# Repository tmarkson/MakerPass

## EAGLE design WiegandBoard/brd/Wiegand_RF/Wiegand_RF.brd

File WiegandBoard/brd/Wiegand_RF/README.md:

#MakerPass Wiegand Board ESP8266

###Tasks
See the schematic for pending task list

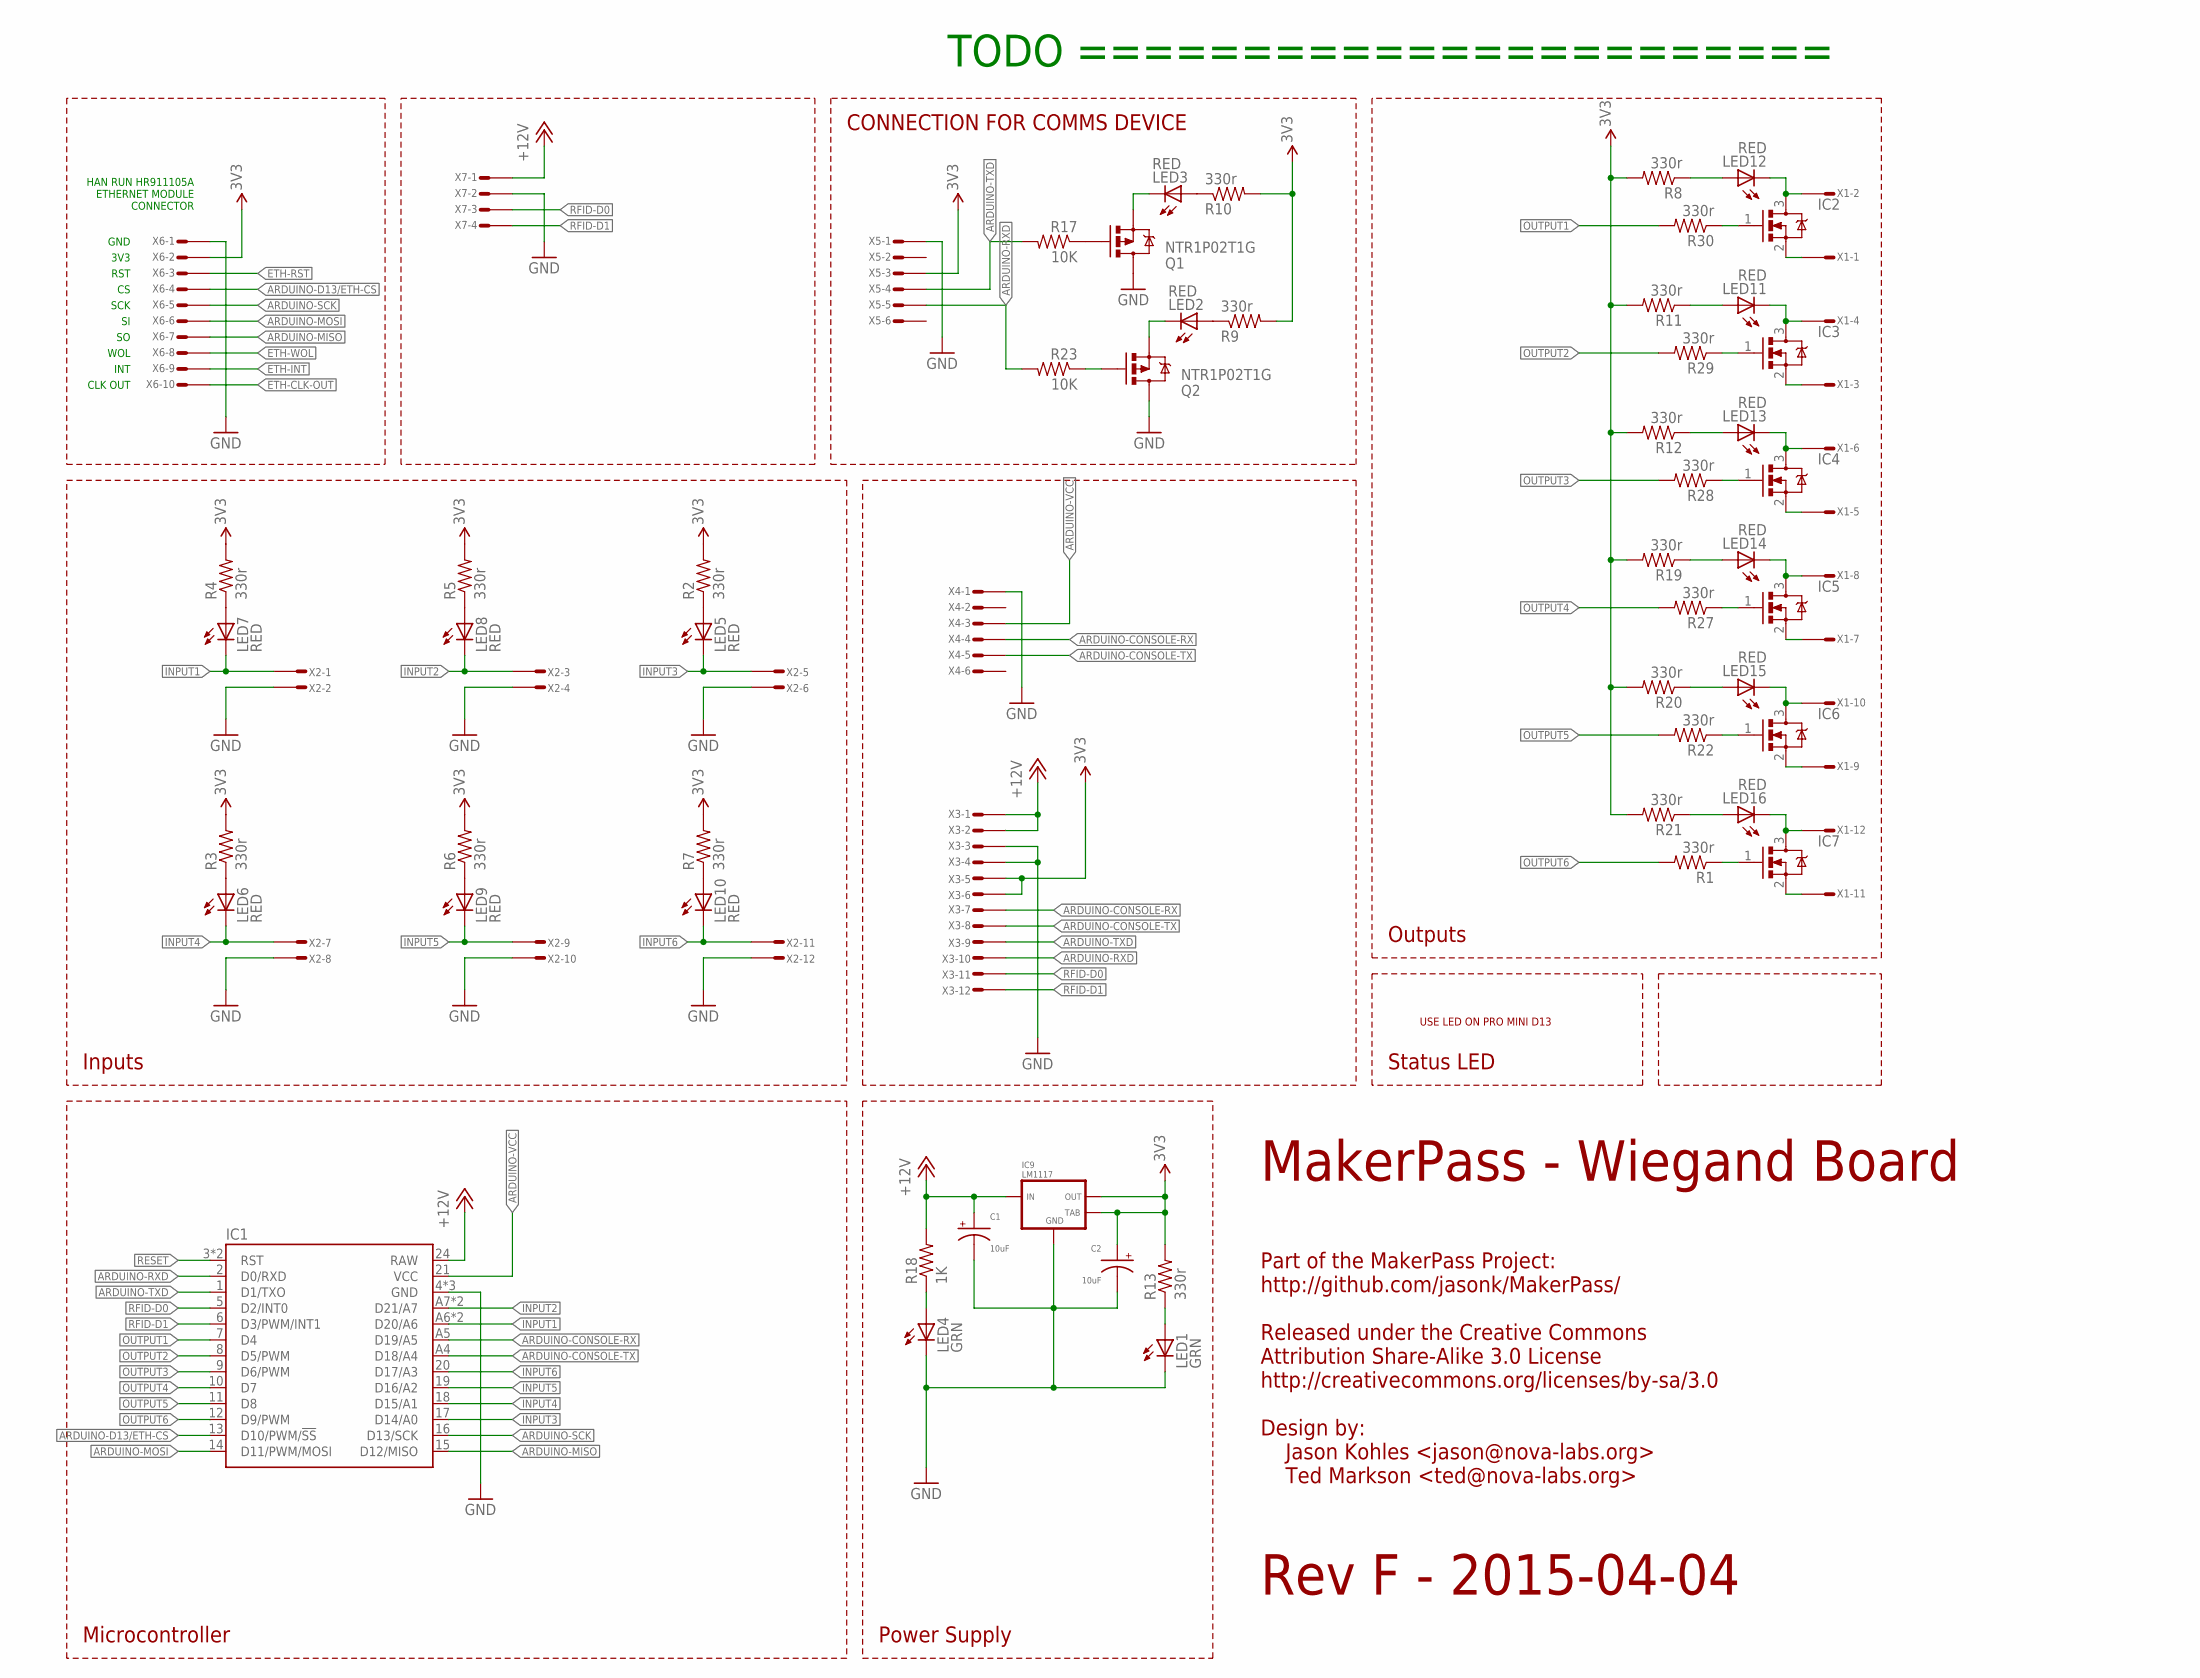
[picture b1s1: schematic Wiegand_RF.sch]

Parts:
C1, C2: 10uF; C-CAN-4.3; MFG_PN EMVA250ADA100MD55G
IC1: ARDUINO-PRO-MINI-ALIEXPRESS
IC2, IC3, IC4, IC5, IC6, IC7: MOSFET-NCHANNEL-SOT23; SOT23
IC9: LM1117; SOT223; MFG_PN LM1117MPX-3.3/NOPB
LED1, LED4: GRN; LED-805; MFG_PN LG R971-KN-1
LED2, LED3, LED5, LED6, LED7, LED8, LED9, LED10, LED11, LED12, LED13, LED14, LED15, LED16: RED; LED-805; MFG_PN LY R976-PS-36
Q1, Q2: NTR1P02T1G; SOT23-3; MFG_PN NTR1P02T1G
R1, R2, R3, R4, R5, R6, R7, R8, R9, R10, R11, R12, R13, R19, R20, R21, R22, R27, R28, R29, R30: 330r; 0603-RES; MFG_PN ERJ3EKF3300V
R17, R23: 10K; 0603-RES; MFG_PN ERJ3EKF1002V
R18: 1K; 0603-RES; MFG_PN ERJ3EKF1001V
X1, X2, X3: CON-1X12-TERMBLOCK-3.5MM; MFG_PN OSTTE120104
X4, X5: CON-1X6-FTDI-AVR
X6: CON-2X5
X7: CON-1X4

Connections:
3V3: C2.+, IC9.OUT, IC9.TAB, R2.2, R3.2, R4.2, R5.2, R6.2, R7.2, R8.2, R9.2, R10.2, R11.2, R12.2, R13.2, R19.2, R20.2, R21.2, X3.5, X3.6, X5.3, X6.2
+12V: C1.+, IC1.24 (RAW), IC9.IN, R18.2, X3.1, X3.2, X7.1
ARDUINO-CONSOLE-RX: IC1.A5 (D19/A5), X3.7, X4.4
ARDUINO-CONSOLE-TX: IC1.A4 (D18/A4), X3.8, X4.5
ARDUINO-D13/ETH-CS: IC1.13 (D10/PWM/!SS), X6.4
ARDUINO-MISO: IC1.15 (D12/MISO), X6.7
ARDUINO-MOSI: IC1.14 (D11/PWM/MOSI), X6.6
ARDUINO-RXD: IC1.2 (D0/RXD), R23.2, X3.10, X5.5
ARDUINO-SCK: IC1.16 (D13/SCK), X6.5
ARDUINO-TXD: IC1.1 (D1/TXO), R17.2, X3.9, X5.4
ARDUINO-VCC: IC1.21 (VCC), X4.3
ETH-CLK-OUT: X6.10
ETH-INT: X6.9
ETH-RST: X6.3
ETH-WOL: X6.8
GND: C1.-, C2.-, IC1.4 (GND), IC1.23 (GND), IC1.25 (GND), IC9.GND, LED1.C, LED4.C, Q1.3 (D), Q2.3 (D), X2.2, X2.4, X2.6, X2.8, X2.10, X2.12, X3.3, X3.4, X4.1, X5.1, X6.1, X7.2
INPUT1: IC1.A6 (D20/A6), IC1.A6@2 (D20/A6), LED7.C, X2.1
INPUT2: IC1.A7 (D21/A7), IC1.A7@2 (D21/A7), LED8.C, X2.3
INPUT3: IC1.17 (D14/A0), LED5.C, X2.5
INPUT4: IC1.18 (D15/A1), LED6.C, X2.7
INPUT5: IC1.19 (D16/A2), LED9.C, X2.9
INPUT6: IC1.20 (D17/A3), LED10.C, X2.11
unnamed: LED1.A, R13.1
unnamed: IC6.2 (S), X1.9
unnamed: IC6.3 (D), LED15.C, X1.10
unnamed: LED5.A, R2.1
unnamed: LED4.A, R18.1
unnamed: LED3.C, Q1.2 (S)
unnamed: LED6.A, R3.1
unnamed: LED7.A, R4.1
unnamed: LED8.A, R5.1
unnamed: LED9.A, R6.1
unnamed: LED10.A, R7.1
unnamed: LED12.A, R8.1
unnamed: IC2.2 (S), X1.1
unnamed: IC2.3 (D), LED12.C, X1.2
unnamed: IC3.2 (S), X1.3
unnamed: IC4.3 (D), LED13.C, X1.6
unnamed: LED11.A, R11.1
unnamed: IC4.2 (S), X1.5
unnamed: LED13.A, R12.1
unnamed: LED2.A, R9.1
unnamed: LED3.A, R10.1
unnamed: IC5.2 (S), X1.7
unnamed: IC5.3 (D), LED14.C, X1.8
unnamed: LED14.A, R19.1
unnamed: LED2.C, Q2.2 (S)
unnamed: Q1.1 (G), R17.1
unnamed: LED15.A, R20.1
unnamed: IC7.2 (S), X1.11
unnamed: IC7.3 (D), LED16.C, X1.12
unnamed: LED16.A, R21.1
unnamed: IC7.1 (G), R1.1
unnamed: Q2.1 (G), R23.1
unnamed: IC2.1 (G), R30.1
unnamed: IC3.1 (G), R29.1
unnamed: IC4.1 (G), R28.1
unnamed: IC5.1 (G), R27.1
unnamed: IC6.1 (G), R22.1
unnamed: IC3.3 (D), LED11.C, X1.4
OUTPUT1: IC1.7 (D4), R30.2
OUTPUT2: IC1.8 (D5/PWM), R29.2
OUTPUT3: IC1.9 (D6/PWM), R28.2
OUTPUT4: IC1.10 (D7), R27.2
OUTPUT5: IC1.11 (D8), R22.2
OUTPUT6: IC1.12 (D9/PWM), R1.2
RESET: IC1.3 (RST), IC1.22 (RST)
RFID-D0: IC1.5 (D2/INT0), X3.11, X7.3
RFID-D1: IC1.6 (D3/PWM/INT1), X3.12, X7.4

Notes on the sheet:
CONNECTION FOR COMMS DEVICE
Power Supply
Part of the MakerPass Project: http://github.com/jasonk/MakerPass/ Released under the Creative Commons Attribution Share-Alike 3.0 License http://creativecommons.org/licenses/by-sa/3.0 Design by: Jason Kohles <jason@nova-labs.org> Ted Markson <ted@nova-labs.org>
Status LED
Outputs
Inputs
Microcontroller
MakerPass - Wiegand Board
Rev F - 2015-04-04
TODO =======================
USE LED ON PRO MINI D13
HAN RUN HR911105A ETHERNET MODULE CONNECTOR
GND
3V3
RST
SCK
WOL
INT
CLK OUT

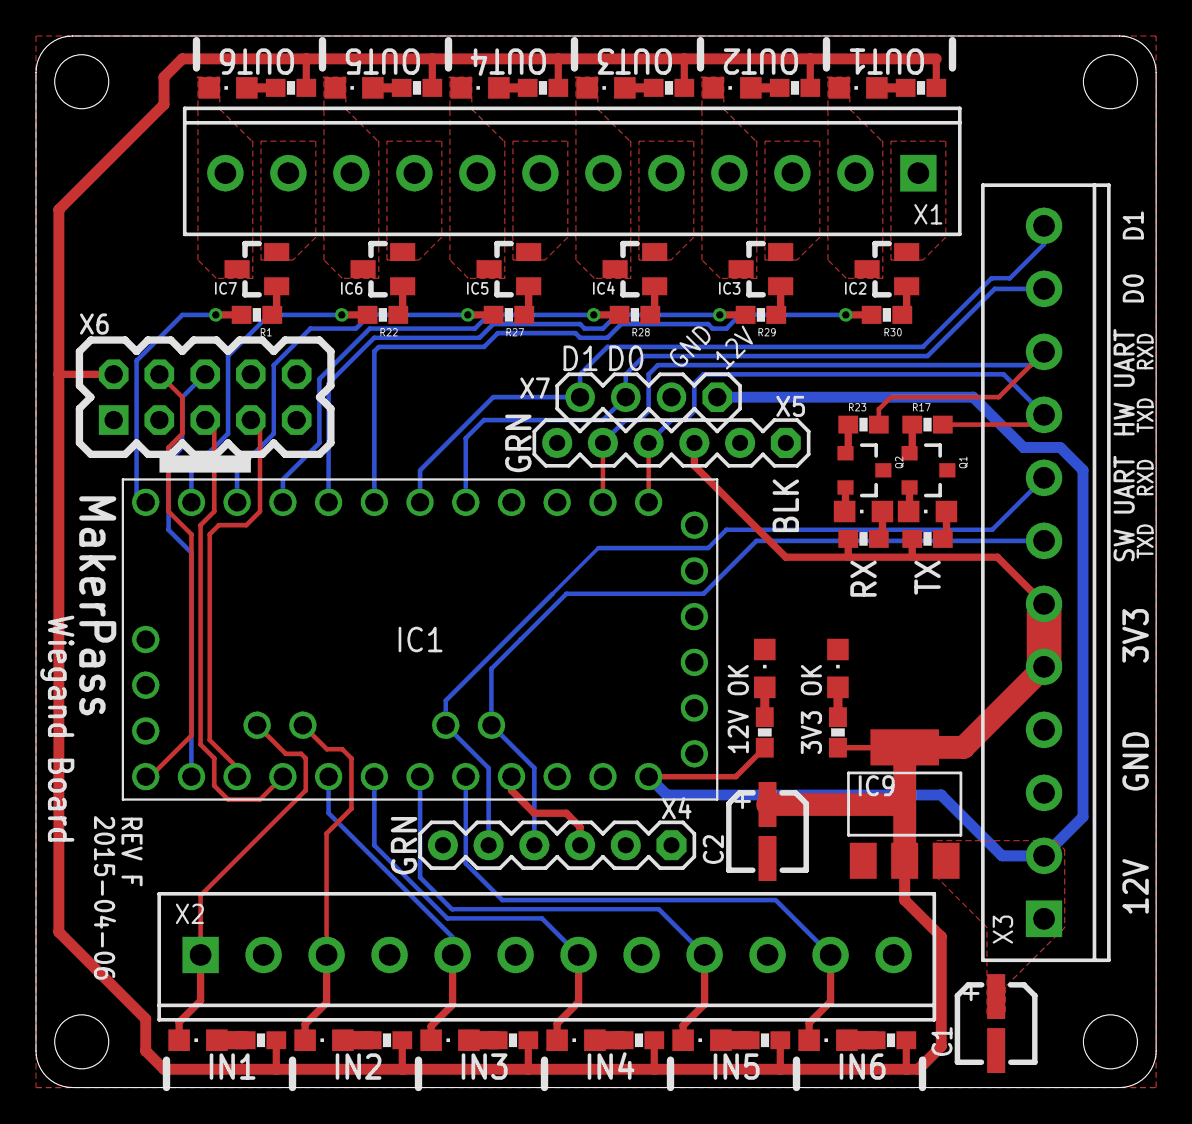
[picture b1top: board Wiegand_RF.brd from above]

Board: 2 copper layers, 62.2 x 58.4 mm, 60 parts (1 on the bottom side), 65 nets.

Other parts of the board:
U$1: NOVA-LABS-LOGO-FULL-SMALL

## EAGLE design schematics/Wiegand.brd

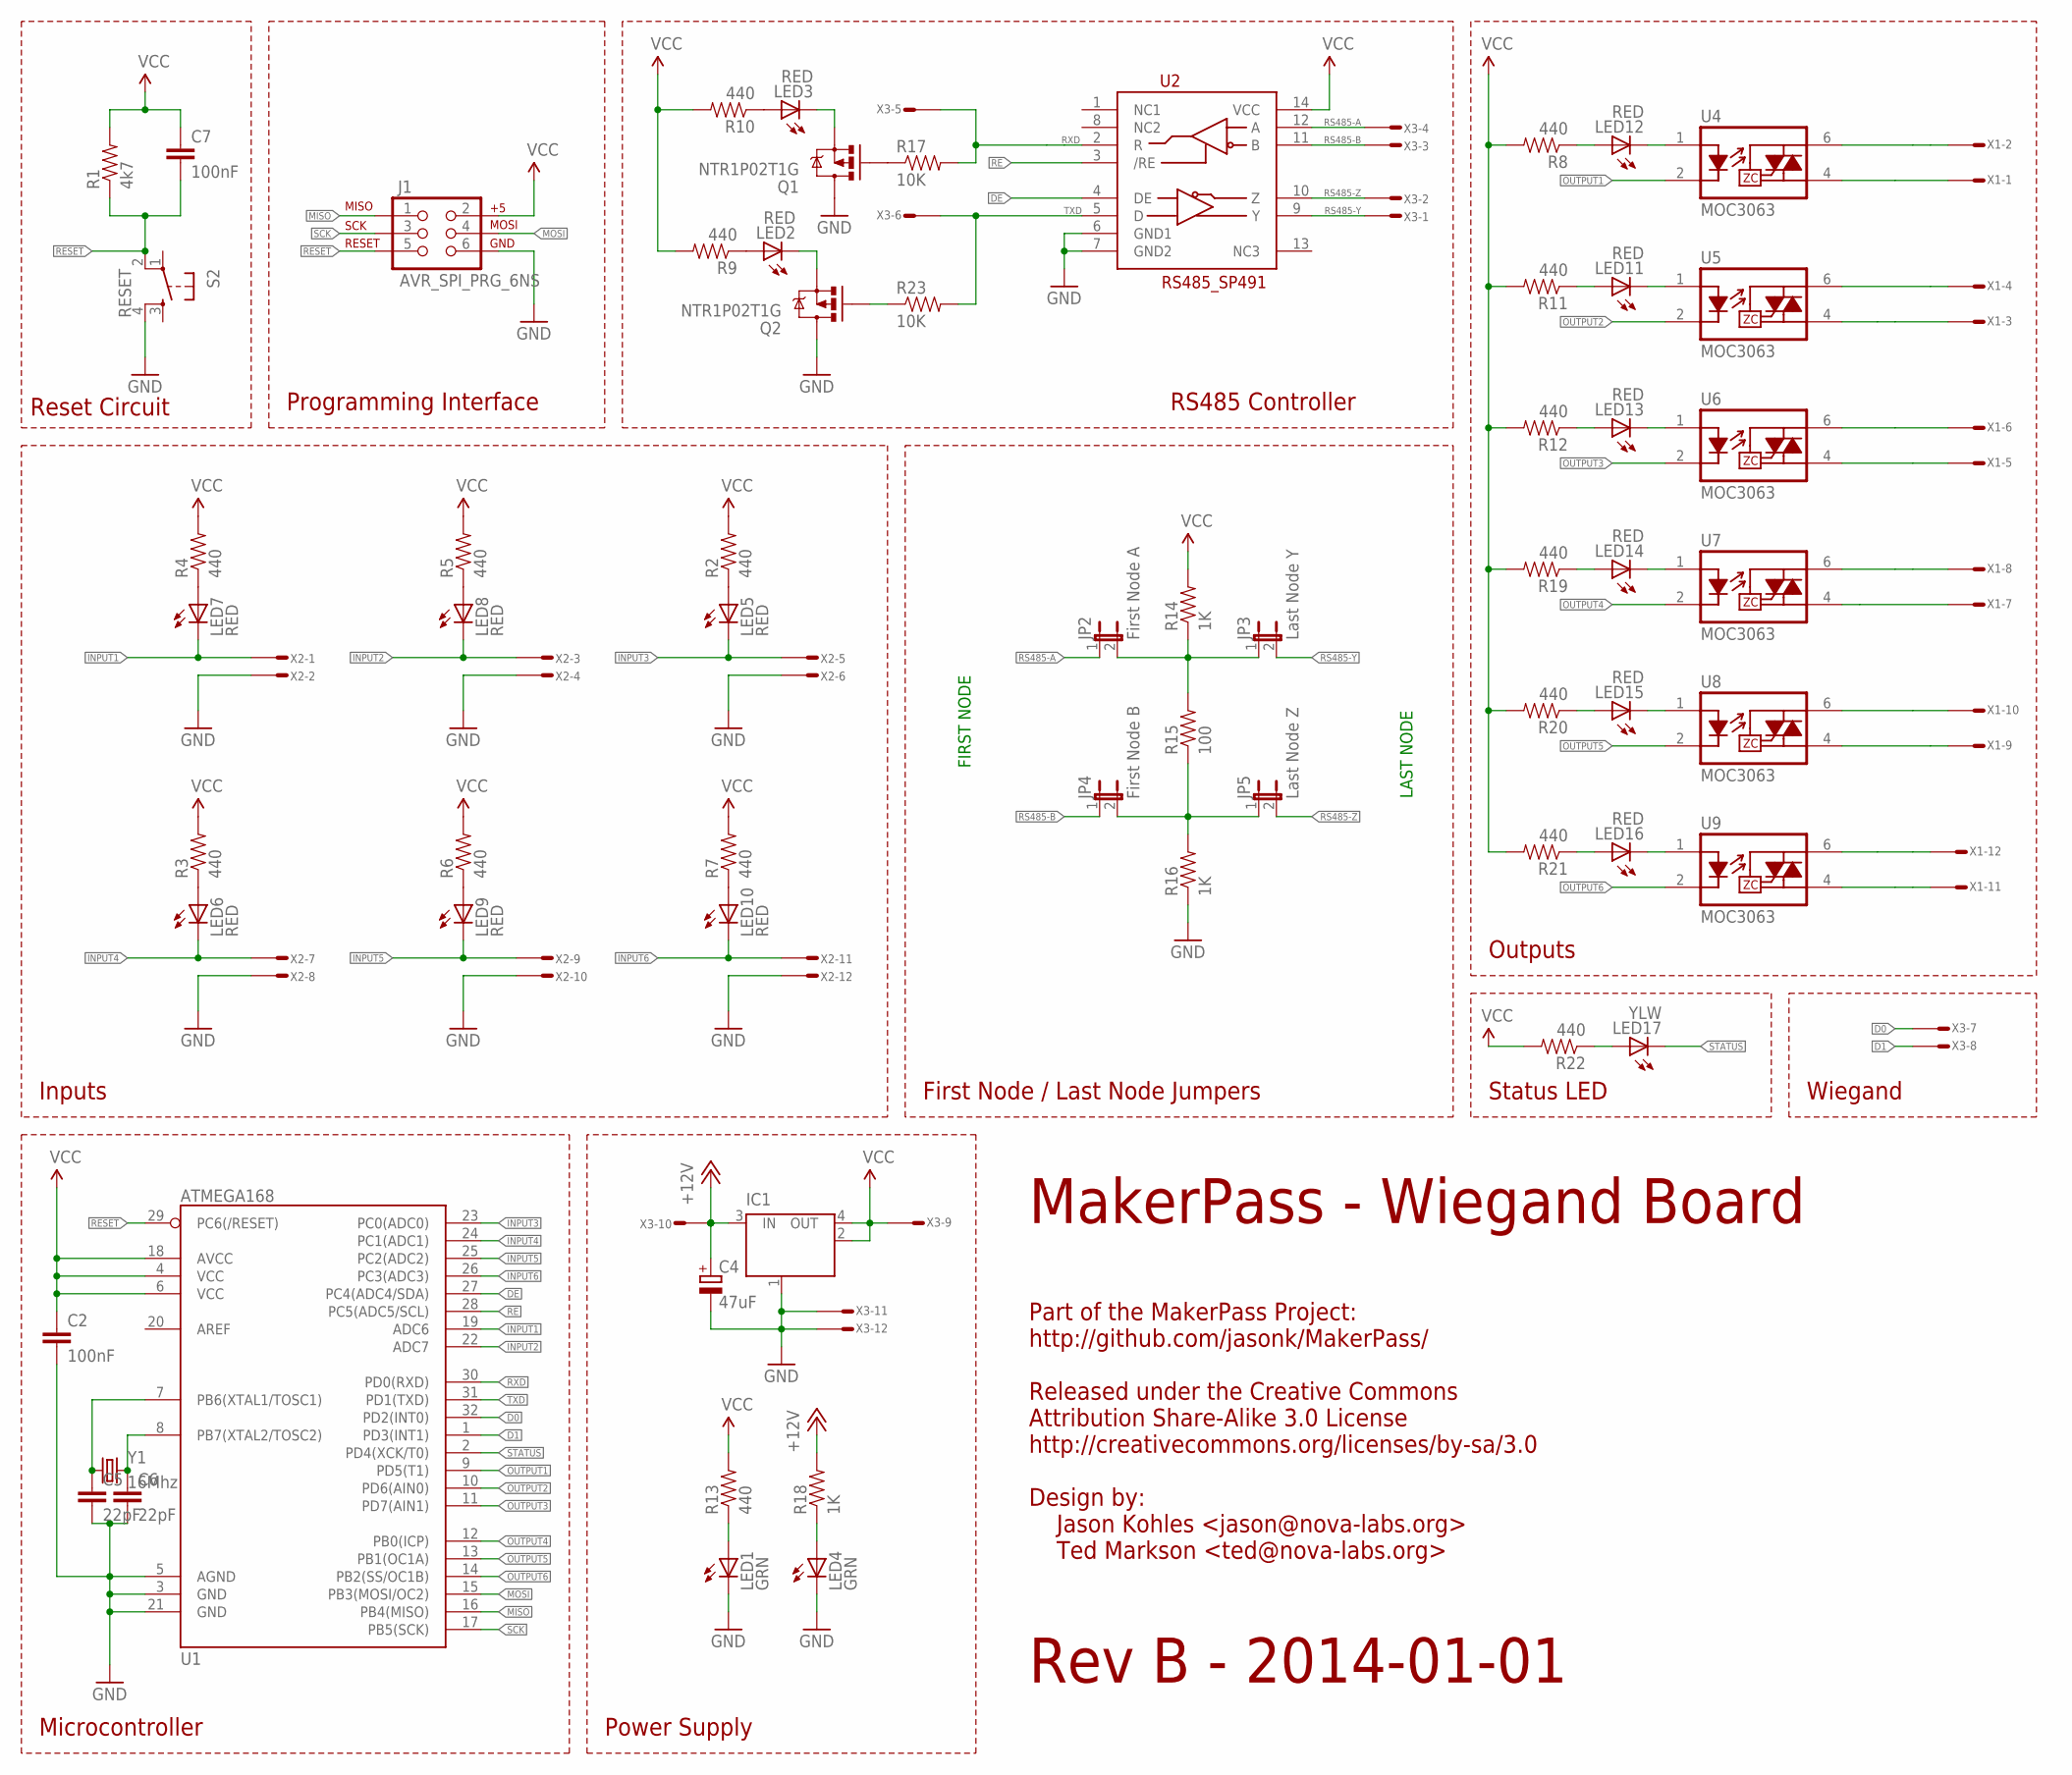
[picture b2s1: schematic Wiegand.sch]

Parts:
C2, C7: 100nF; 0603-CAP; MFG_PN 0603YC104KAT2A
C4: 47uF; PANASONIC_D; MFG_PN EMVA250ADA470MF55G
C5, C6: 22pF; 0603-CAP; MFG_PN 06035A220JAT2A
IC1: MC33269ST-3.3T3; SOT223; MFG_PN NCP1117ST50T3G
J1: AVR_SPI_PRG_6NS; 2X3-NS
JP2: First Node A; 1X02; MFG_PN 1x2 pin header
JP3: Last Node Y; 1X02; MFG_PN 1x2 pin header
JP4: First Node B; 1X02; MFG_PN 1x2 pin header
JP5: Last Node Z; 1X02; MFG_PN 1x2 pin header
LED1, LED4: GRN; LED-805; MFG_PN LG R971-KN-1
LED2, LED3, LED5, LED6, LED7, LED8, LED9, LED10, LED11, LED12, LED13, LED14, LED15, LED16: RED; LED-805; MFG_PN LY R976-PS-36
LED17: YLW; LED-805; MFG_PN LY R976-PS-36
Q1, Q2: NTR1P02T1G; SOT23-3; MFG_PN NTR1P02T1G
R1: 4k7; 0603-RES; MFG_PN ERJ-3GEYJ472V
R2, R3, R4, R5, R6, R7, R8, R9, R10, R11, R12, R13, R19, R20, R21, R22: 440; 0603-RES; MFG_PN ERJ3EKF3300V
R14, R16, R18: 1K; 0603-RES; MFG_PN ERJ-3EKF1001V
R15: 100; 0603-RES; MFG_PN ERJ-3EKF1001V
R17, R23: 10K; 0603-RES; MFG_PN ERJ3EKF3300V
S2: RESET; TACTILE_SWITCH_SMD; MFG_PN PTS525SM10SMTRLFS
U1: ATMEGA168; TQFP32-08; MFG_PN ATMEGA168-20AU
U2: RS485_SP491; SOIC-14; MFG_PN SP491EEN-L
U4, U5, U6, U7, U8, U9: MOC3063; DIP8SMD; MFG_PN MOC3063M
X1, X2, X3: CON-1X12-TERMBLOCK-3.5MM; MFG_PN OSTTE120104
Y1: 16Mhz; HC49UP; MFG_PN FOXSDLF/160-20

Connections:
+12V: C4.+, IC1.3 (IN), R18.2, X3.10
D0: U1.32 (PD2(INT0)), X3.7
D1: U1.1 (PD3(INT1)), X3.8
DE: U1.27 (PC4(ADC4/SDA)), U2.4 (DE)
GND: C2.2, C4.-, C5.2, C6.2, IC1.1 (GND/ADJ), J1.6, LED1.C, LED4.C, Q1.3 (D), Q2.3 (D), R16.1, S2.4, U1.3 (GND), U1.5 (AGND), U1.21 (GND), U2.6 (GND1), U2.7 (GND2), X2.2, X2.4, X2.6, X2.8, X2.10, X2.12, X3.11, X3.12
INPUT1: LED7.C, U1.19 (ADC6), X2.1
INPUT2: LED8.C, U1.22 (ADC7), X2.3
INPUT3: LED5.C, U1.23 (PC0(ADC0)), X2.5
INPUT4: LED6.C, U1.24 (PC1(ADC1)), X2.7
INPUT5: LED9.C, U1.25 (PC2(ADC2)), X2.9
INPUT6: LED10.C, U1.26 (PC3(ADC3)), X2.11
MISO: J1.1, U1.16 (PB4(MISO))
MOSI: J1.4, U1.15 (PB3(MOSI/OC2))
unnamed: LED1.A, R13.1
unnamed: U8.4 (T2), X1.9
unnamed: U8.6 (T1), X1.10
unnamed: LED5.A, R2.1
unnamed: JP4.2, JP5.1, R15.1, R16.2
unnamed: JP2.2, JP3.1, R14.1, R15.2
unnamed: LED4.A, R18.1
unnamed: LED3.C, Q1.2 (S)
unnamed: LED6.A, R3.1
unnamed: LED7.A, R4.1
unnamed: LED8.A, R5.1
unnamed: LED9.A, R6.1
unnamed: LED10.A, R7.1
unnamed: LED12.C, U4.1 (A)
unnamed: LED12.A, R8.1
unnamed: U4.4 (T2), X1.1
unnamed: U4.6 (T1), X1.2
unnamed: U5.4 (T2), X1.3
unnamed: U5.6 (T1), X1.4
unnamed: LED11.A, R11.1
unnamed: LED11.C, U5.1 (A)
unnamed: U6.4 (T2), X1.5
unnamed: U6.6 (T1), X1.6
unnamed: LED13.A, R12.1
unnamed: LED2.A, R9.1
unnamed: LED3.A, R10.1
unnamed: LED13.C, U6.1 (A)
unnamed: U7.4 (T2), X1.7
unnamed: U7.6 (T1), X1.8
unnamed: LED14.A, R19.1
unnamed: LED14.C, U7.1 (A)
unnamed: LED2.C, Q2.2 (S)
unnamed: Q1.1 (G), R17.1
unnamed: LED15.A, R20.1
unnamed: LED15.C, U8.1 (A)
unnamed: U9.4 (T2), X1.11
unnamed: U9.6 (T1), X1.12
unnamed: LED16.A, R21.1
unnamed: LED16.C, U9.1 (A)
unnamed: LED17.A, R22.1
unnamed: Q2.1 (G), R23.1
unnamed: C5.1, U1.7 (PB6(XTAL1/TOSC1)), Y1.1
unnamed: C6.1, U1.8 (PB7(XTAL2/TOSC2)), Y1.2
OUTPUT1: U1.9 (PD5(T1)), U4.2 (K)
OUTPUT2: U1.10 (PD6(AIN0)), U5.2 (K)
OUTPUT3: U1.11 (PD7(AIN1)), U6.2 (K)
OUTPUT4: U1.12 (PB0(ICP)), U7.2 (K)
OUTPUT5: U1.13 (PB1(OC1A)), U8.2 (K)
OUTPUT6: U1.14 (PB2(SS/OC1B)), U9.2 (K)
RE: U1.28 (PC5(ADC5/SCL)), U2.3 (/RE)
RESET: C7.2, J1.5, R1.1, S2.2, U1.29 (PC6(/RESET))
RS485-A: JP2.1, U2.12 (A), X3.4
RS485-B: JP4.1, U2.11 (B), X3.3
RS485-Y: JP3.2, U2.9 (Y), X3.1
RS485-Z: JP5.2, U2.10 (Z), X3.2
RXD: R17.2, U1.30 (PD0(RXD)), U2.2 (R), X3.5
SCK: J1.3, U1.17 (PB5(SCK))
STATUS: LED17.C, U1.2 (PD4(XCK/T0))
TXD: R23.2, U1.31 (PD1(TXD)), U2.5 (D), X3.6
VCC: C2.1, C7.1, IC1.2 (OUT), IC1.4 (OUT), J1.2, R1.2, R2.2, R3.2, R4.2, R5.2, R6.2, R7.2, R8.2, R9.2, R10.2, R11.2, R12.2, R13.2, R14.2, R19.2, R20.2, R21.2, R22.2, U1.4 (VCC), U1.6 (VCC), U1.18 (AVCC), U2.14 (VCC), X3.9

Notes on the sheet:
RS485 Controller
Programming Interface
Power Supply
Reset Circuit
Wiegand
Part of the MakerPass Project: http://github.com/jasonk/MakerPass/ Released under the Creative Commons Attribution Share-Alike 3.0 License http://creativecommons.org/licenses/by-sa/3.0 Design by: Jason Kohles <jason@nova-labs.org> Ted Markson <ted@nova-labs.org>
Status LED
First Node / Last Node Jumpers
Outputs
Inputs
Microcontroller
MakerPass - Wiegand Board
Rev B - 2014-01-01
FIRST NODE
LAST NODE

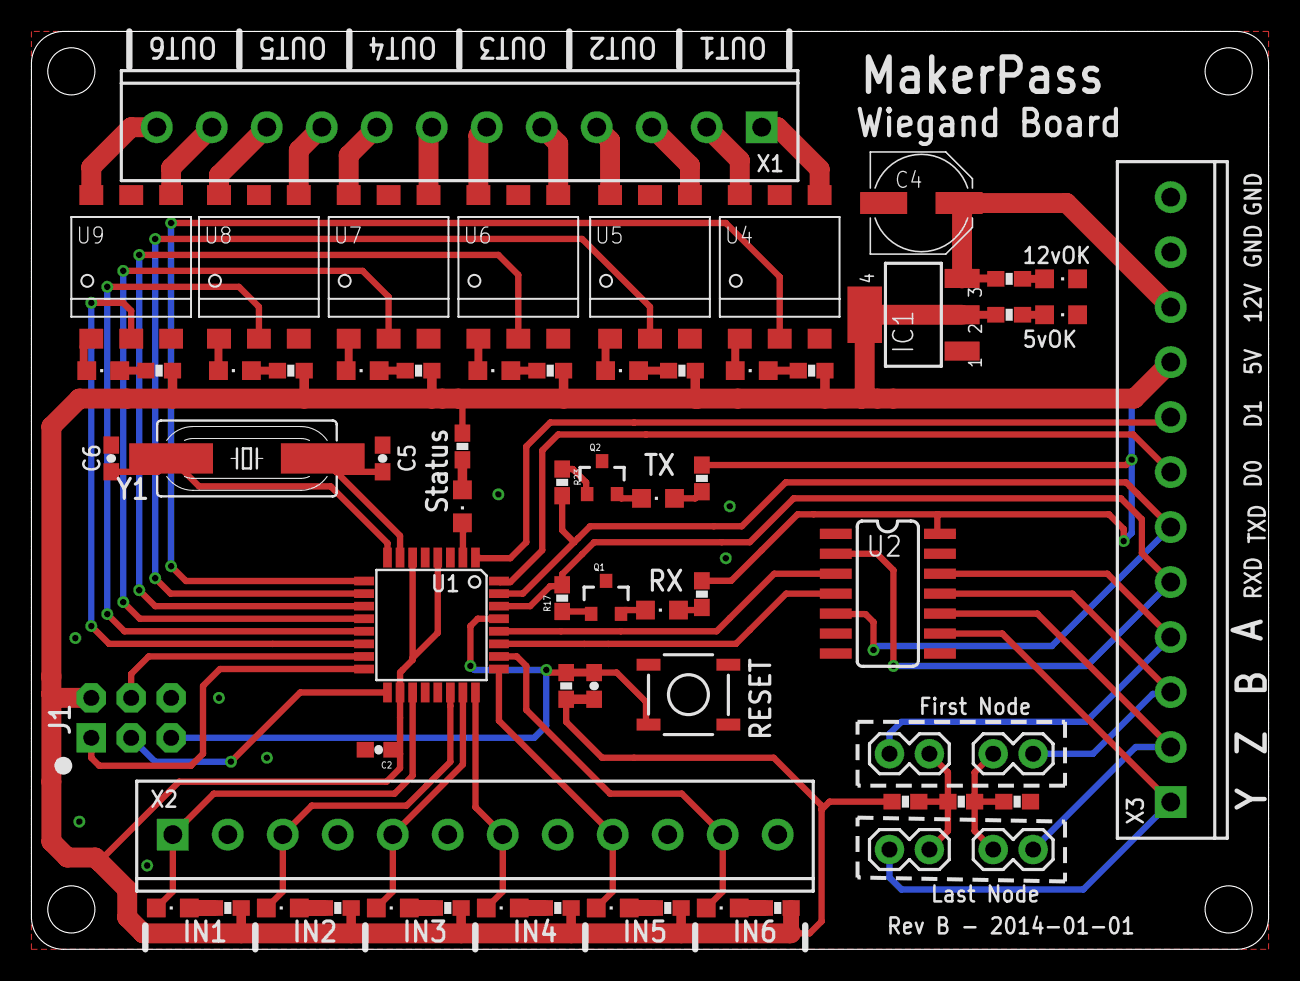
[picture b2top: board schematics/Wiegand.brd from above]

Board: 2 copper layers, 78.7 x 58.4 mm, 67 parts (1 on the bottom side), 73 nets.

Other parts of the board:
U$4: NOVALABS

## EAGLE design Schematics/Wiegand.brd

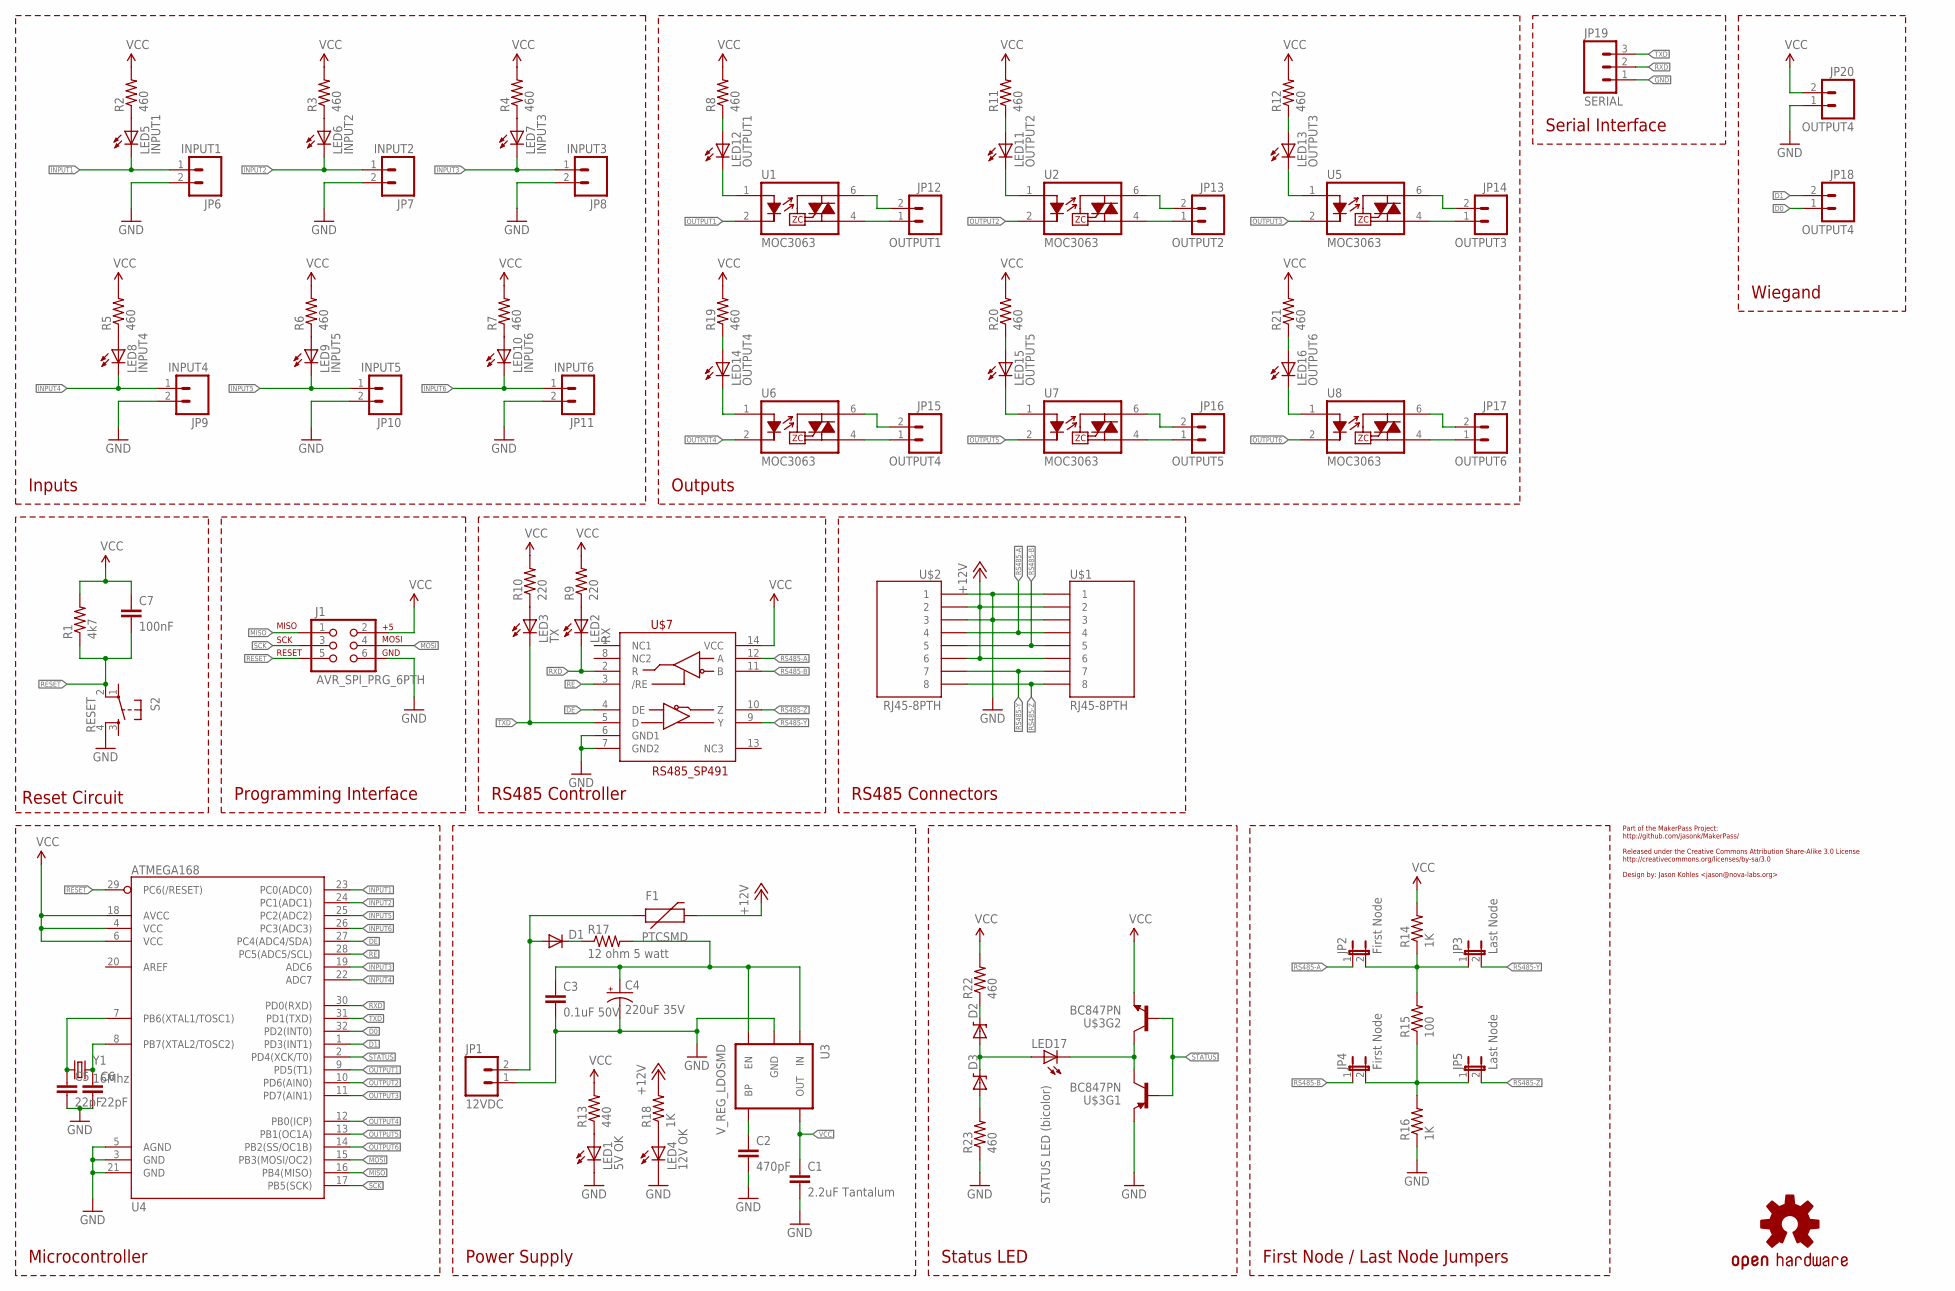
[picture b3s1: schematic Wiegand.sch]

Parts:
C1: 2.2uF Tantalum; 0402-CAP
C2: 470pF; 0402-CAP
C3: 0.1uF 50V; 0402-CAP
C4: 220uF 35V; VISHAY_C
C5, C6: 22pF; 0603-CAP
C7: 100nF; 0603-CAP
D1: DIODESMA; SMA-DIODE
D2, D3: DIODE-ZENER-BZT52; SOD-323
F1: PTCSMD; PTC-1206
J1: AVR_SPI_PRG_6PTH; 2X3
JP1: 12VDC; SCREWTERMINAL-5MM-2
JP2, JP4: First Node; 1X02
JP3, JP5: Last Node; 1X02
JP6: INPUT1; SCREWTERMINAL-3.5MM-2
JP7: INPUT2; SCREWTERMINAL-3.5MM-2
JP8: INPUT3; SCREWTERMINAL-3.5MM-2
JP9: INPUT4; SCREWTERMINAL-3.5MM-2
JP10: INPUT5; SCREWTERMINAL-3.5MM-2
JP11: INPUT6; SCREWTERMINAL-3.5MM-2
JP12: OUTPUT1; SCREWTERMINAL-3.5MM-2
JP13: OUTPUT2; SCREWTERMINAL-3.5MM-2
JP14: OUTPUT3; SCREWTERMINAL-3.5MM-2
JP15, JP18, JP20: OUTPUT4; SCREWTERMINAL-3.5MM-2
JP16: OUTPUT5; SCREWTERMINAL-3.5MM-2
JP17: OUTPUT6; SCREWTERMINAL-3.5MM-2
JP19: SERIAL; 1X03
LED1: 5V OK; LED-1206
LED2: RX; LED-1206
LED3: TX; LED-1206
LED4: 12V OK; LED-1206
LED5: INPUT1; LED-1206
LED6: INPUT2; LED-1206
LED7: INPUT3; LED-1206
LED8: INPUT4; LED-1206
LED9: INPUT5; LED-1206
LED10: INPUT6; LED-1206
LED11: OUTPUT2; LED-1206
LED12: OUTPUT1; LED-1206
LED13: OUTPUT3; LED-1206
LED14: OUTPUT4; LED-1206
LED15: OUTPUT5; LED-1206
LED16: OUTPUT6; LED-1206
LED17: STATUS LED (bicolor); LED-1206
LOGO1: OSHW-LOGOM; OSHW-LOGO-M
R1: 4k7; 0603-RES
R2, R3, R4, R5, R6, R7, R8, R11, R12, R19, R20, R21, R22, R23: 460; 0603-RES
R9, R10: 220; 0603-RES
R13: 440; 0603-RES
R14, R16, R18: 1K; 0603-RES
R15: 100; 0603-RES
R17: 12 ohm 5 watt; 0603-RES
S2: RESET; TACTILE_SWITCH_SMD
U1, U2, U5, U6, U7, U8: MOC3063; DIP8SMD
U3: V_REG_LDOSMD; SOT23-5
U4: ATMEGA168; TQFP32-08
U$1, U$2: RJ45-8PTH; RJ45-8
U$3: BC847PN; SOT363
U$7: RS485_SP491; SOIC-14
Y1: 16Mhz; HC49UP

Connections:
12V_IN: D1.A, F1.1, JP1.2
+12V: F1.2, R18.2, U$1.2, U$1.6, U$2.2, U$2.6
D0: JP18.1, U4.32 (PD2(INT0))
D1: JP18.2, U4.1 (PD3(INT1))
DE: U4.27 (PC4(ADC4/SDA)), U$7.4 (DE)
GND: C1.2, C2.2, C3.2, C4.-, C5.2, C6.2, J1.6, JP1.1, JP6.2, JP7.2, JP8.2, JP9.2, JP10.2, JP11.2, JP19.1, JP20.1, LED1.C, LED4.C, R16.1, R23.1, S2.4, U3.2 (GND), U4.3 (GND), U4.5 (AGND), U4.21 (GND), U$1.1, U$1.3, U$2.1, U$2.3, U$3.1 (E), U$7.6 (GND1), U$7.7 (GND2)
INPUT1: JP6.1, LED5.C, U4.23 (PC0(ADC0))
INPUT2: JP7.1, LED6.C, U4.24 (PC1(ADC1))
INPUT3: JP8.1, LED7.C, U4.19 (ADC6)
INPUT4: JP9.1, LED8.C, U4.22 (ADC7)
INPUT5: JP10.1, LED9.C, U4.25 (PC2(ADC2))
INPUT6: JP11.1, LED10.C, U4.26 (PC3(ADC3))
MISO: J1.1, U4.16 (PB4(MISO))
MOSI: J1.4, U4.15 (PB3(MOSI/OC2))
unnamed: LED1.A, R13.1
unnamed: C2.1, U3.4 (BP)
unnamed: C3.1, C4.+, R17.2, U3.1 (IN), U3.3 (EN)
unnamed: LED5.A, R2.1
unnamed: JP4.2, JP5.1, R15.1, R16.2
unnamed: JP2.2, JP3.1, R14.1, R15.2
unnamed: LED4.A, R18.1
unnamed: D1.C, R17.1
unnamed: LED6.A, R3.1
unnamed: LED7.A, R4.1
unnamed: LED8.A, R5.1
unnamed: LED9.A, R6.1
unnamed: LED10.A, R7.1
unnamed: LED12.C, U1.1 (A)
unnamed: LED12.A, R8.1
unnamed: JP12.1, U1.4 (T2)
unnamed: JP12.2, U1.6 (T1)
unnamed: JP13.1, U2.4 (T2)
unnamed: JP13.2, U2.6 (T1)
unnamed: LED11.A, R11.1
unnamed: LED11.C, U2.1 (A)
unnamed: JP14.1, U5.4 (T2)
unnamed: JP14.2, U5.6 (T1)
unnamed: LED13.A, R12.1
unnamed: LED2.A, R9.1
unnamed: LED3.A, R10.1
unnamed: LED13.C, U5.1 (A)
unnamed: JP15.1, U6.4 (T2)
unnamed: JP15.2, U6.6 (T1)
unnamed: LED14.A, R19.1
unnamed: LED14.C, U6.1 (A)
unnamed: JP16.1, U7.4 (T2)
unnamed: JP16.2, U7.6 (T1)
unnamed: LED15.A, R20.1
unnamed: LED15.C, U7.1 (A)
unnamed: JP17.1, U8.4 (T2)
unnamed: JP17.2, U8.6 (T1)
unnamed: LED16.A, R21.1
unnamed: LED16.C, U8.1 (A)
unnamed: D2.1 (C), R22.1
unnamed: D2.2 (A), D3.1 (C), LED17.A
unnamed: D3.2 (A), R23.2
unnamed: LED17.C, U$3.3 (C), U$3.6 (C)
unnamed: C5.1, U4.7 (PB6(XTAL1/TOSC1)), Y1.1
unnamed: C6.1, U4.8 (PB7(XTAL2/TOSC2)), Y1.2
OUTPUT1: U1.2 (K), U4.9 (PD5(T1))
OUTPUT2: U2.2 (K), U4.10 (PD6(AIN0))
OUTPUT3: U4.11 (PD7(AIN1)), U5.2 (K)
OUTPUT4: U4.12 (PB0(ICP)), U6.2 (K)
OUTPUT5: U4.13 (PB1(OC1A)), U7.2 (K)
OUTPUT6: U4.14 (PB2(SS/OC1B)), U8.2 (K)
RE: U4.28 (PC5(ADC5/SCL)), U$7.3 (/RE)
RESET: C7.2, J1.5, R1.1, S2.2, U4.29 (PC6(/RESET))
RS485-A: JP2.1, U$1.4, U$2.4, U$7.12 (A)
RS485-B: JP4.1, U$1.5, U$2.5, U$7.11 (B)
RS485-Y: JP3.2, U$1.7, U$2.7, U$7.9 (Y)
RS485-Z: JP5.2, U$1.8, U$2.8, U$7.10 (Z)
RXD: JP19.2, LED2.C, U4.30 (PD0(RXD)), U$7.2 (R)
SCK: J1.3, U4.17 (PB5(SCK))
STATUS: U4.2 (PD4(XCK/T0)), U$3.2 (B), U$3.5 (B)
TXD: JP19.3, LED3.C, U4.31 (PD1(TXD)), U$7.5 (D)
VCC: C1.1, C7.1, J1.2, JP20.2, R1.2, R2.2, R3.2, R4.2, R5.2, R6.2, R7.2, R8.2, R9.2, R10.2, R11.2, R12.2, R13.2, R14.2, R19.2, R20.2, R21.2, R22.2, U3.5 (OUT), U4.4 (VCC), U4.6 (VCC), U4.18 (AVCC), U$3.4 (E), U$7.14 (VCC)

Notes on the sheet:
RS485 Controller
Programming Interface
Power Supply
Reset Circuit
RS485 Connectors
Serial Interface
Part of the MakerPass Project: http://github.com/jasonk/MakerPass/ Released under the Creative Commons Attribution Share-Alike 3.0 License http://creativecommons.org/licenses/by-sa/3.0 Design by: Jason Kohles <jason@nova-labs.org>
Status LED
First Node / Last Node Jumpers
Outputs
Inputs
Microcontroller
Wiegand

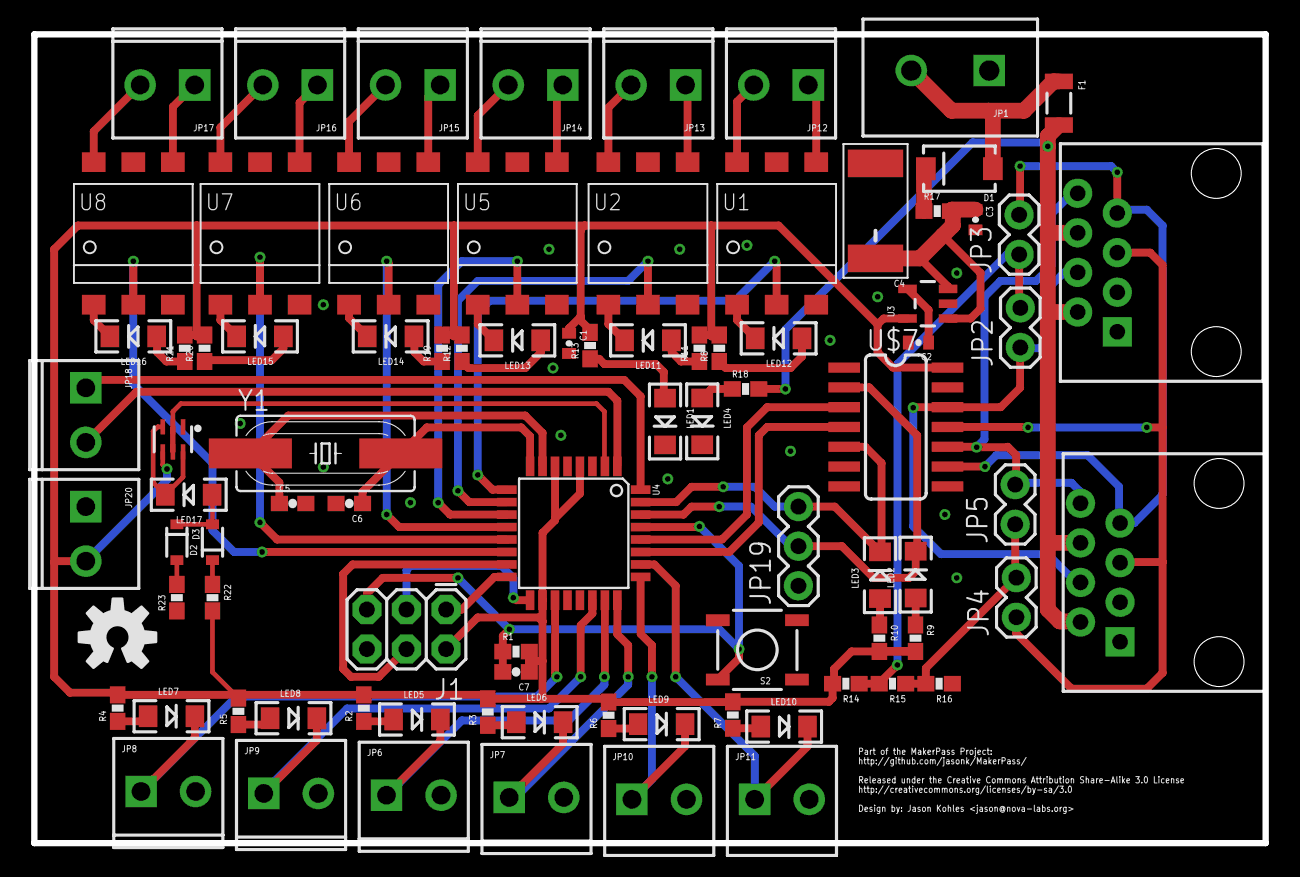
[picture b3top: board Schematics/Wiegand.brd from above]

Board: 2 copper layers, 79.0 x 51.9 mm, 88 parts (1 on the bottom side), 76 nets.

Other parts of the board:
U$4: NOVALABS

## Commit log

2013-11-30 Checking initial Wiegand schematic
2013-12-14 updated schematics and added bom
2013-12-17 Remove bom.txt
2014-01-05 Board Rev B
2015-02-28 integrating ted\'s files including "RF" and "RS485" editions
2015-02-28 futzing with _RF edition to remove reference to another git repo
2015-02-28 adding _RF edition back in - initial commit
2015-04-27 cleaned rs485 files, updated RF version for production - REV F

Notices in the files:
parts and their libraries:
SparkFun: Licensing: CC v3.0 Share-Alike You are welcome to use this library for commercial purposes.
